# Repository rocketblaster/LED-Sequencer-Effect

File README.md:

# LED Sequencer Effect

This is an LED sequencer circuit shaped airplane with LEDs lighting up the fiery engines. Running on 5 volts, it is made with 3x LEDs, transistors and resistors of different levels. It works by lighting up one LED at a time to represent the heat from the engine going up one by one! Tried to get an effect of moving fire but this is closest I managed to get.

---

## Simulation

The circuit works as an astable multivibrator, meaning after a specific duration the led goes into an active and non active state temporarily. There is a switch in place if I don't want power to the LEDs while connected to power. How it works is it in parallel and one of the LEDs lights up then goes off. Because the capacitor stores energy and the transistors have a base starting from capacitor and LED it moves from one LED to the next so that the current can turn it on.

[Link to Demo](https://is.gd/a9qMvy)

---
## Schematic

## PCB

---

This was super paintstaking to make but I pushed through anyways yay!

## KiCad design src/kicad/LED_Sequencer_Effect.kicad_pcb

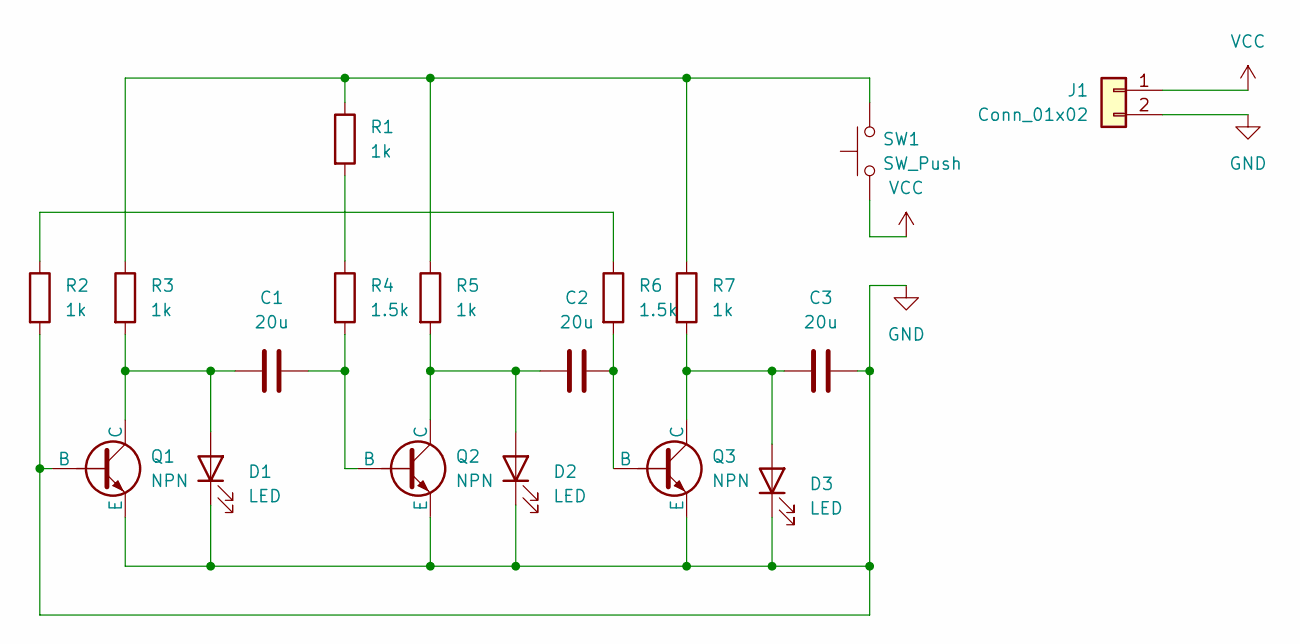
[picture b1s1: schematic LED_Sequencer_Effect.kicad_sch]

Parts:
C1, C2, C3: 20u; C_Disc_D5.0mm_W2.5mm_P5.00mm
D1, D2, D3: LED; LED_D5.0mm
J1: Conn_01x02; PinHeader_1x02_P2.54mm_Vertical
Q1, Q2, Q3: NPN; TO-92L_Inline_Wide
R1, R2, R3, R5, R7: 1k; R_Axial_DIN0204_L3.6mm_D1.6mm_P7.62mm_Horizontal
R4, R6: 1.5k; R_Axial_DIN0204_L3.6mm_D1.6mm_P7.62mm_Horizontal
SW1: SW_Push; SW_PUSH_6mm

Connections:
GND: C3.2, D1.1 (K), D2.1 (K), D3.1 (K), J1.2, Q1.2 (B), Q1.3 (E), Q2.3 (E), Q3.3 (E), R2.2
unnamed: C1.1, D1.2 (A), Q1.1 (C), R3.2
unnamed: C2.1, D2.2 (A), Q2.1 (C), R5.2
unnamed: C3.1, D3.2 (A), Q3.1 (C), R7.2
unnamed: C1.2, Q2.2 (B), R4.2
unnamed: C2.2, Q3.2 (B), R6.2
unnamed: R1.1, R3.1, R5.1, R7.1, SW1.2
unnamed: R1.2, R4.1
unnamed: R2.1, R6.1
VCC: J1.1, SW1.1

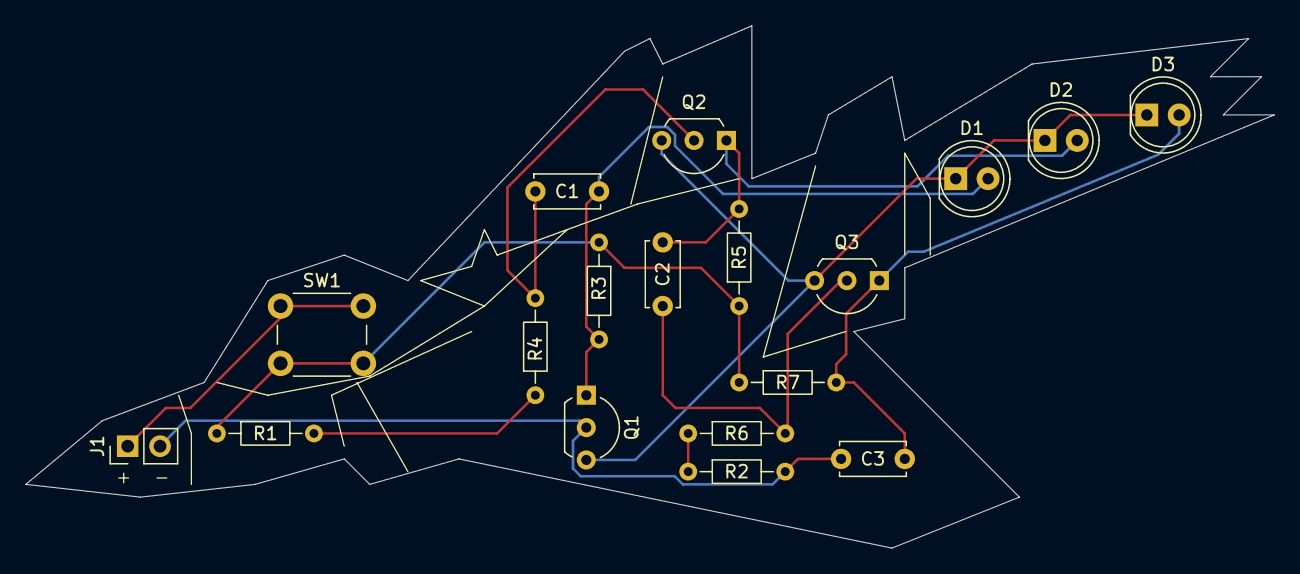
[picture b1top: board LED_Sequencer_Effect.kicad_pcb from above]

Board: 2 copper layers, 98.0 x 41.0 mm, 18 parts (0 on the bottom side), 10 nets.

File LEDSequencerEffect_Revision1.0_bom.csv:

Designator,Footprint,Quantity,Value,LCSC Part #
"C1, C2, C3",C_Disc_D5.0mm_W2.5mm_P5.00mm,3,20u,
"D1, D2, D3",LED_D5.0mm,3,LED,
J1,PinHeader_1x02_P2.54mm_Vertical,1,Conn_01x02,
"Q1, Q2, Q3",TO-92L_Inline_Wide,3,NPN,
"R1, R2, R3, R5, R7",R_Axial_DIN0204_L3.6mm_D1.6mm_P7.62mm_Horizontal,5,1k,
"R4, R6",R_Axial_DIN0204_L3.6mm_D1.6mm_P7.62mm_Horizontal,2,1.5k,
SW1,SW_PUSH_6mm,1,SW_Push,

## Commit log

2026-03-29 Rename LED sequencer.txt to src/falstad/LED Sequencer.txt
2026-03-30 Create test
2026-03-30 Rename LEDSequencerEffect_Revision1.0_positions.csv to production/LEDSequencerEffect_Revision1.0_positions.csv
2026-03-30 Rename LEDSequencerEffect_Revision1.0_designators.csv to production/LEDSequencerEffect_Revision1.0_designators.csv
2026-03-30 Rename LEDSequencerEffect_Revision1.0_bom.csv to production/LEDSequencerEffect_Revision1.0_bom.csv
2026-03-30 Rename LEDSequencerEffect_Revision1.0.zip to production/LEDSequencerEffect_Revision1.0.zip
2026-03-30 Rename netlist.ipc to production/netlist.ipc
